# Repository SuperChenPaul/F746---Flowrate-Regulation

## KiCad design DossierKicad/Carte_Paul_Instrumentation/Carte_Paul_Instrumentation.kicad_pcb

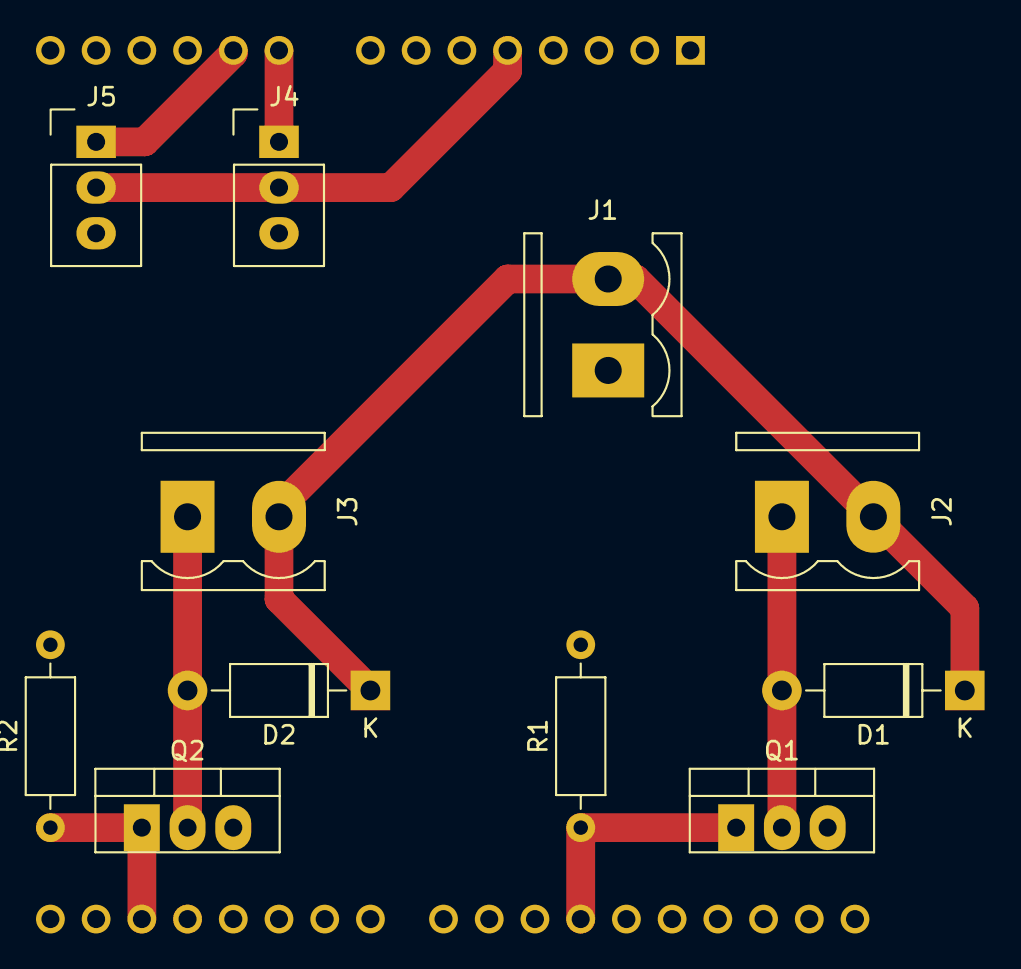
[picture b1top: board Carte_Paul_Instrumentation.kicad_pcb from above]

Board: 2 copper layers, 12 parts (1 on the bottom side), 9 nets.

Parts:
A1: Arduino_UNO_R3
D1, D2: 1N400X; D_DO-41_SOD81_P10.16mm_Horizontal
J1, J2, J3: Omnimate2; OmnimateSL-5,08_1x02_P5.08mm_Vertical
J4, J5: Autocom3
Q1, Q2: IRL510; TO-220-3_Vertical
R1, R2: R; R_Axial_DIN0207_L6.3mm_D2.5mm_P10.16mm_Horizontal

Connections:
+5V: A1.5 (+5V), J4.2, J5.2
+12V: D1.1 (K), D2.1 (K), J1.2, J2.2, J3.2
/A0: A1.9 (A0), J4.1
/A1: A1.10 (A1), J5.1
/D2: A1.17 (D2), Q2.1 (G), R2.1
/D11: A1.26 (D11), Q1.1 (G), R1.1
GND: A1.29 (GND), J1.1, J4.3, J5.3, Q1.3 (S), Q2.3 (S), R1.2, R2.2
unnamed: D1.2 (A), J2.1, Q1.2 (D)
unnamed: D2.2 (A), J3.1, Q2.2 (D)

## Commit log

2023-05-31 Added Input/Output
2023-05-31 Added test of Output Input
2023-06-06 Added UI Interface
2023-06-07 Added interactive UI
2023-06-11 salut
2023-06-14 Final version
2023-06-19 Added commentary
2023-06-20 V1.0
2023-06-25 Kicad
2023-06-25 Main
